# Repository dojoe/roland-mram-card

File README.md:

# Roland compatible multi-bank MRAM memory card

 (click to enlarge)

This is a replacement memory card for old Roland instruments of the late 80s and early 90s, such as the D-50 synthesizers, the JV-1080 and JV-2080 rack synths or the JD-880. It is meant to replace memory cards of the M-128, M-256 and M-512 lines (including M-256E, M-512G and all other suffixes). Some Akai devices from the same age actually use a compatible card format (BR-16 and BR-32) and this card will work in those too.

It doesn't need any kind of backup battery since it uses non-volatile MRAM for data storage, and thanks to the large memory chip used it emulates multiple virtual cards ("banks") which are selectable via slide switches - one of these memory cards will emulate 8x M-512 or 16x M-256 depending on the setting of a solder jumper.

The card has been developed with a lot of testing help from the community over at [the VintageSynth forums](https://forum.vintagesynth.com/viewtopic.php?f=24&t=76886) and over 900 units have been manufactured and sold since then - with near zero complaints :) Since the beginning of the project, we had plans to eventually publish the design data and source code for the card so it would stay available to everyone once we stopped making and selling them. So here it is!

## Compatibility

* **Tested and fully compatible:** Roland A-90, D-5, D-20, D-50, D-550, D-10, D-110, D-70, U-20, JD-800, JD-990, JV-880, JV-1000, JV-1080, JV-2080, R-880 (GC-8), R-8M, GR-1, GR-50, PM-16, TR-626, Akai MX-1000, VX600.
* **Mostly compatible:** Roland TD-10, TD-20. The card reportedly has errors when inserted all the way, but pulled back 1/8th of an inch it works fine.
* **Not compatible:** Roland VG-8, Peavey Tubefex.
* Some units like the Roland U-110 and U-220 only accept ROM cards, not RAM cards. Naturally, this RAM card replacement does not work in those, either.

## Differences to the cards we sell

Functionally, this design is 100% identical to the cards we sell online. I did make some changes to the appearance however to make homemade cards clearly distinguishable from ours.

Also, one part we use (a Bourns CAT25 SMD resistor network) is no longer being manufactured, so I updated the BOM with a Panasonic part as a drop-in replacement.

## Directories

* [mram-card](mram-card): The memory card hardware design files.
* [datasheets](datasheets): Data sheets for most of the parts used.
* [testbench](testbench): The testbench I'm using to test every card before they go out to customers.

## Making cards

Send the [KiCAD PCB file](mram-card/d50mram.kicad_pcb) or the [Gerbers](mram-card/gerbers.zip) to your favorite board house - or order directly from OSHPark:

<a href="https://oshpark.com/shared_projects/AyL7HCIK"></img></a>

As for parts, check out the [bill of materials](mram-card/d50mram.bom.csv).

Did you build one, or even more than one? We'd love to hear from you, feel free to leave a comment in the [card builder thread](https://github.com/dojoe/roland-mram-card/issues/2) :)

# Licenses

## Memory card

<br /><span xmlns:dct="http://purl.org/dc/terms/" property="dct:title">The hardware design of the <a href="https://github.com/dojoe/roland-mram-card">Roland compatible multi-bank MRAM memory card</a></span> by <a xmlns:cc="http://creativecommons.org/ns#" href="https://github.com/dojoe" property="cc:attributionName" rel="cc:attributionURL">Joachim "dojoe" Fenkes</a> is licensed under a <a rel="license" href="http://creativecommons.org/licenses/by-sa/4.0/">Creative Commons Attribution-ShareAlike 4.0 International License</a>.

## Testbench

Please see the [testbench README](testbench/README.md) for testbench license information.

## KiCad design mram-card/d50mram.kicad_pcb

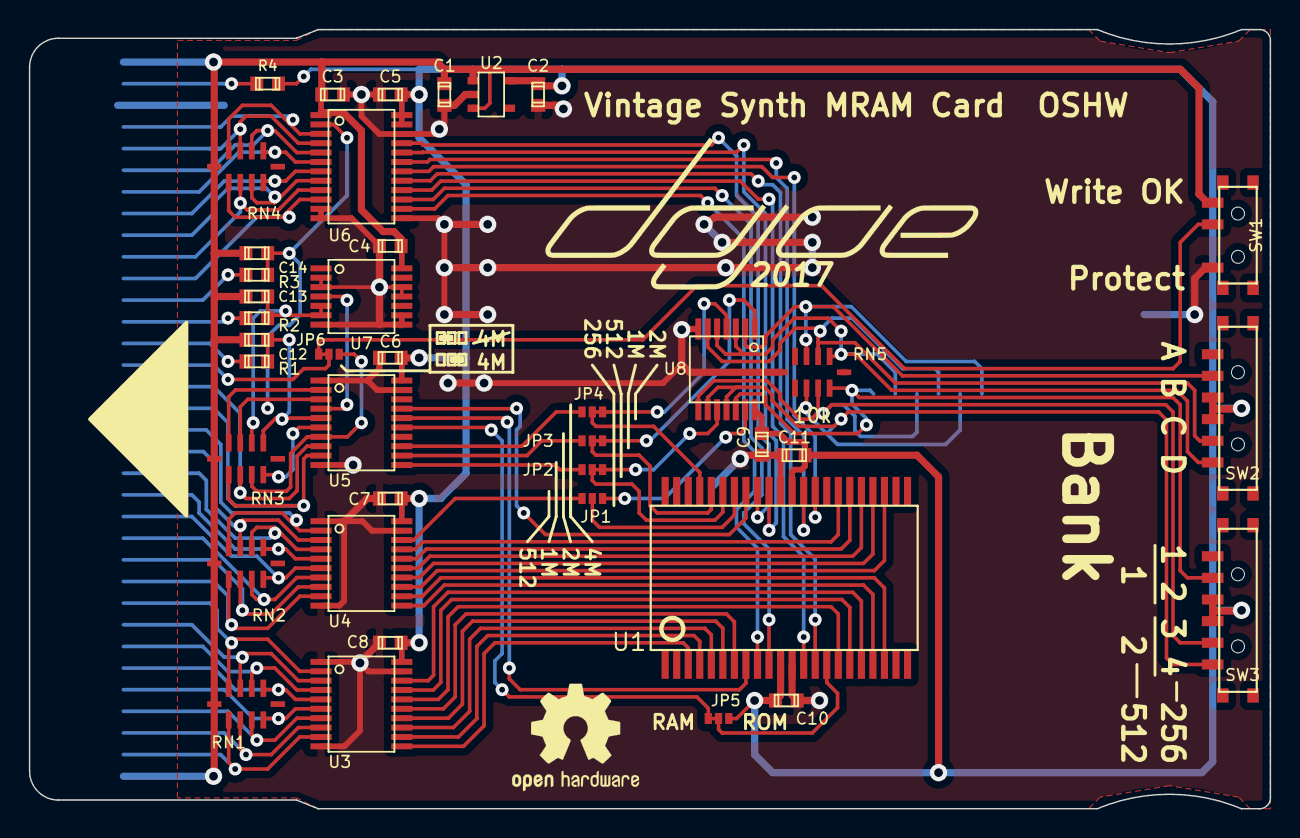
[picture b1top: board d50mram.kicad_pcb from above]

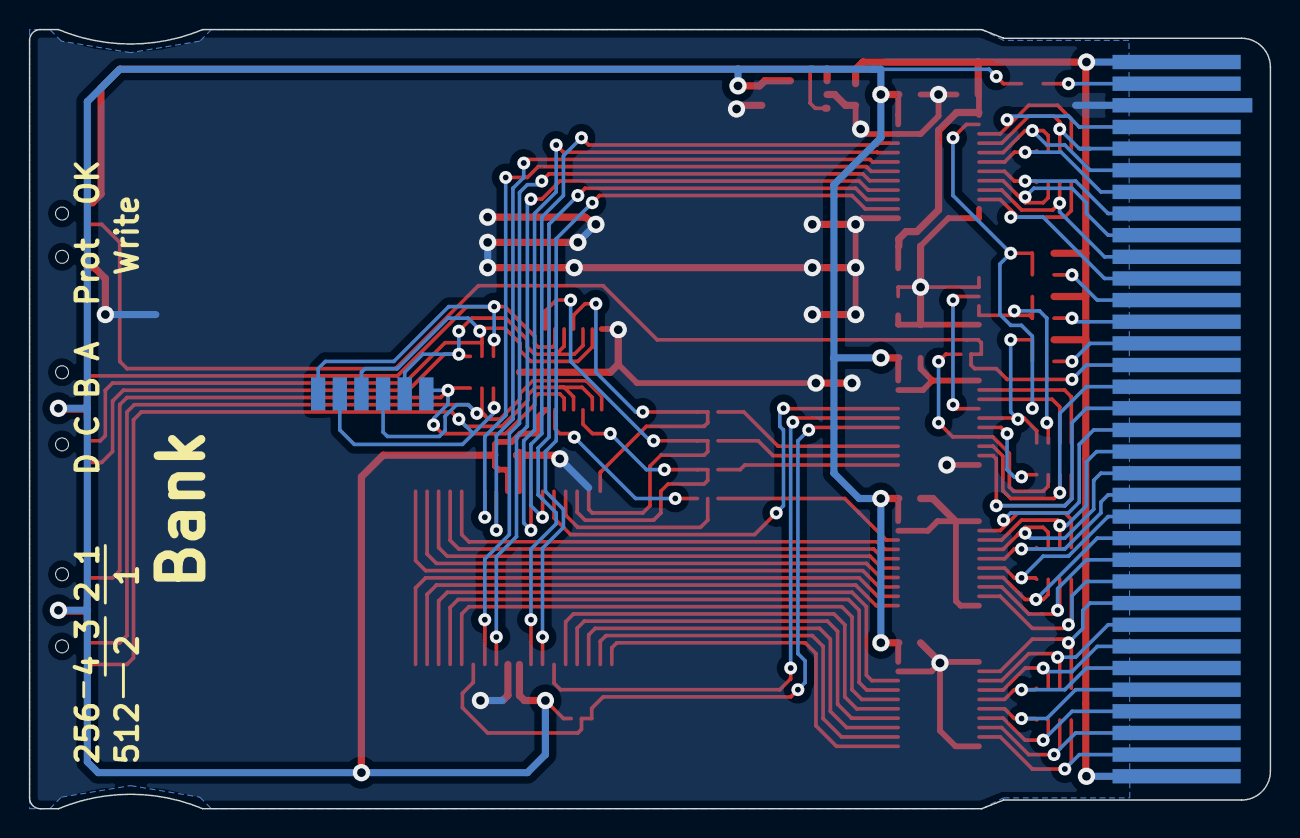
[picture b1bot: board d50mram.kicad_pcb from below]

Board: 2 copper layers, 86.0 x 54.0 mm, 43 parts (2 on the bottom side), 82 nets.

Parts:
C1, C2: 1uF X7R; c_0603
C3, C4, C5, C6, C7, C8, C9, C10, C11: 100n; c_0603
C12, C13, C14: 100p; c_0603
J1: D50-EDGECONN; EDGE1S34
JP1, JP2, JP3, JP4, JP5, JP6: JUMPER3; S_JUMPER_3
R1, R2, R3, R4: 100R; c_0603
RN1, RN2, RN3, RN4, RN5: 10k; CAT25
SW1: SPDT; CUS-12B
SW2, SW3: SP4T; CUS-14B
TP1: CONN_6; 6P_TESTPT
U1: EST-MR2A08A; TSOP2-44
U2: MIC5265-3.3YD5; SOT23-5
U3, U4, U5: 74LVX541; tssop-20
U6: 74LVX4245; tssop-24
U7, U8: 74HC02; tssop-14
VAL: REF; dojoe

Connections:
+3.3V: C2.1, C5.1, C6.1, C7.1, C8.1, C9.1, C10.1, C11.1, JP5.1, R4.2, SW2.1, SW3.1, U1.11, U1.33, U2.5, U3.20, U4.20, U5.20, U6.23, U6.24, U8.14
+5V: C1.1, C3.1, C4.1, C12.2, C13.2, C14.2, J1.1, J1.34, RN1.1, RN2.1, RN3.1, RN4.1, SW1.2, U2.1, U2.3, U6.1, U7.14
/A0C: J1.2, RN1.7, U3.9
/A0M: U1.3, U3.11
/A1C: J1.3, RN1.8, U3.8
/A1M: U1.4, U3.12
/A2C: J1.4, RN1.9, U3.7
/A2M: U1.5, U3.13
/A3C: J1.5, RN1.10, U3.6
/A3M: U1.6, U3.14
/A4C: J1.6, RN1.2, U3.5
/A4M: U1.7, U3.15
/A5C: J1.7, RN1.3, U3.4
/A5M: U1.16, U3.16
/A6C: J1.8, RN1.4, U3.3
/A6M: U1.17, U3.17
/A7C: J1.9, RN1.5, U3.2
/A7M: U1.18, U3.18
/A8C: J1.10, RN2.7, U4.9
/A8M: U1.19, U4.11
/A9C: J1.11, RN2.8, U4.8
/A9M: U1.20, U4.12
/A10C: J1.12, RN2.9, U4.7
/A10M: U1.25, U4.13
/A11C: J1.13, RN2.10, U4.6
/A11M: U1.26, U4.14
/A12C: J1.14, RN2.2, U4.5
/A12M: U1.27, U4.15
/A13C: J1.15, RN2.3, U4.4
/A13M: U1.28, U4.16
/A14C: J1.16, RN2.4, U4.3
/A14M: U1.29, U4.17
/A15C: J1.17, RN2.5, U4.2
/A15M: JP1.2, U1.38
/A15M_C: JP1.1, U4.18
/A15M_SW: JP1.3, U8.13
/A16C: J1.18, RN3.7, U5.9
/A16M: JP2.2, JP2.3, U1.39, U8.10
/A16M_C: JP2.1, U5.11
/A17C: J1.19, RN3.8, U5.8
/A17M: JP3.2, JP3.3, U1.40, U8.1
/A17M_C: JP3.1, U5.12
/A18C: JP6.3, RN3.9, U5.7
/A18M: JP4.2, JP4.3, U1.41, U8.4
/A18M_C: JP4.1, U5.13
/BANK2: RN5.5, SW3.3, TP1.1, U8.12
/BANK3: RN5.4, SW3.4, TP1.3, U8.8
/BANK4: RN5.3, SW3.5, TP1.5, U8.9, U8.11
/BANKB: RN5.9, SW2.3, TP1.6, U8.2
/BANKC: RN5.8, SW2.4, TP1.4, U8.6
/BANKD: RN5.7, SW2.5, TP1.2, U8.3, U8.5
/CEC: J1.22, R2.1
/D0C: J1.24, RN4.7, U6.10
/D0M: U1.9, U6.14
/D1C: J1.25, RN4.8, U6.9
/D1M: U1.10, U6.15
/D2C: J1.26, RN4.9, U6.8
/D2M: U1.13, U6.16
/D3C: J1.27, RN4.10, U6.7
/D3M: U1.14, U6.17
/D4C: J1.28, RN4.2, U6.6
/D4M: U1.31, U6.18
/D5C: J1.29, RN4.3, U6.5
/D5M: U1.32, U6.19
/D6C: J1.30, RN4.4, U6.4
/D6M: U1.35, U6.20
/D7C: J1.31, RN4.5, U6.3
/D7M: U1.36, U6.21
/WR_EN: J1.20, JP6.1, JP6.2, SW1.1
/~CEC: U5.4, U7.4
/~CEM: U1.8, U5.16
/~OEC: J1.23, R3.1
/~OEM: U1.37, U5.17
/~WEC: J1.21, R1.1
/~WEM: JP5.2, JP5.3, U1.15, U5.15
GND: C1.2, C2.2, C3.2, C4.2, C5.2, C6.2, C7.2, C8.2, C9.2, C10.2, C11.2, J1.32, RN5.1, SW1.3, U1.12, U1.34, U2.2, U3.1, U3.10, U3.19, U4.1, U4.10, U4.19, U5.1, U5.10, U5.19, U6.11, U6.12, U6.13, U6.22, U7.2, U7.3, U7.7, U7.8, U7.9, U7.11, U7.12, U8.7
unnamed: C12.1, R1.2, RN3.2, U5.5
unnamed: C13.1, R2.2, RN3.3, U7.5, U7.6
unnamed: C14.1, R3.2, RN3.4, U5.3, U6.2
unnamed: J1.33, R4.1
unnamed: RN3.5, U5.2
unnamed: RN3.10, U5.6

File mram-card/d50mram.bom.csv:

"Source:","D:\Projects\d50_mram_card\opensource\mram-card\d50mram.kicad_sch"
"Date:","2023-01-02 14:01:17"
"Tool:","Eeschema (6.0.7)"
"Generator:","C:\Program Files\KiCad\6.0\bin\scripting\plugins/bom_csv_grouped_by_value.py"
"Component Count:","42"

"Individual Components:"

"Item","Qty","Reference(s)","Value","LibPart","Footprint","Datasheet","Digikey","Mouser"
"","","C1","1uF X7R","d50mram:C","","","",""
"","","C2","1uF X7R","d50mram:C","","","",""
"","","C3","100n","d50mram:C","","","",""
"","","C4","100n","d50mram:C","","","",""
"","","C5","100n","d50mram:C","","","",""
"","","C6","100n","d50mram:C","","","",""
"","","C7","100n","d50mram:C","","","",""
"","","C8","100n","d50mram:C","","","",""
"","","C9","100n","d50mram:C","","","",""
"","","C10","100n","d50mram:C","","","",""
"","","C11","100n","d50mram:C","","","",""
"","","C12","100p","d50mram:C","","","",""
"","","C13","100p","d50mram:C","","","",""
"","","C14","100p","d50mram:C","","","",""
"","","J1","D50-EDGECONN","d50mram:D50-EDGECONN","","","",""
"","","JP1","JUMPER3","d50mram:JUMPER3","","","",""
"","","JP2","JUMPER3","d50mram:JUMPER3","","","",""
"","","JP3","JUMPER3","d50mram:JUMPER3","","","",""
"","","JP4","JUMPER3","d50mram:JUMPER3","","","",""
"","","JP5","JUMPER3","d50mram:JUMPER3","","","",""
"","","JP6","JUMPER3","d50mram:JUMPER3","","","",""
"","","R1","100R","d50mram:R","","","",""
"","","R2","100R","d50mram:R","","","",""
"","","R3","100R","d50mram:R","","","",""
"","","R4","100R","d50mram:R","","","",""
"","","RN1","10k","d50mram:CAT25","","","U8103CT-ND","667-EXB-E10C103J"
"","","RN2","10k","d50mram:CAT25","","","U8103CT-ND","667-EXB-E10C103J"
"","","RN3","10k","d50mram:CAT25","","","U8103CT-ND","667-EXB-E10C103J"
"","","RN4","10k","d50mram:CAT25","","","U8103CT-ND","667-EXB-E10C103J"
"","","RN5","10k","d50mram:CAT25","","","U8103CT-ND","667-EXB-E10C103J"
"","","SW1","SPDT","d50mram:SPDT","","","563-1102-1-ND","229-CUS-12TB"
"","","SW2","SP4T","d50mram:SP4T","","","563-1104-1-ND","229-CUS-14TB"
"","","SW3","SP4T","d50mram:SP4T","","","563-1104-1-ND","229-CUS-14TB"
"","","TP1","CONN_6","d50mram:CONN_6","","","",""
"","","U1","EST-MR2A08A","d50mram:EST-MR2A08A","","","819-1004-ND","936-MR2A08AYS35"
"","","U2","MIC5265-3.3YD5","d50mram:TC1054","","","576-2835-1-ND","998-MIC5265-3.3YD5TR"
"","","U3","74LVX541","d50mram:74LS541","","","74LVX541MTCXCT-ND","512-74LVX541MTCX"
"","","U4","74LVX541","d50mram:74LS541","","","74LVX541MTCXCT-ND","512-74LVX541MTCX"
"","","U5","74LVX541","d50mram:74LS541","","","74LVX541MTCXCT-ND","512-74LVX541MTCX"
"","","U6","74LVX4245","d50mram:74x4245","","","74LVX4245MTCXCT-ND","512-74LVX4245MTCX"
"","","U7","74HC02","d50mram:74LS02P","","","MM74HC02MTCXCT-ND","512-MM74HC02MTCX"
"","","U8","74HC02","d50mram:74LS02P","","","MM74HC02MTCXCT-ND","512-MM74HC02MTCX"



"Collated Components:"

"Item","Qty","Reference(s)","Value","LibPart","Footprint","Datasheet","Digikey","Mouser"
"1","2","C1, C2","1uF X7R","d50mram:C","","","",""
"2","9","C3, C4, C5, C6, C7, C8, C9, C10, C11","100n","d50mram:C","","","",""
"3","3","C12, C13, C14","100p","d50mram:C","","","",""
"4","1","J1","D50-EDGECONN","d50mram:D50-EDGECONN","","","",""
"5","6","JP1, JP2, JP3, JP4, JP5, JP6","JUMPER3","d50mram:JUMPER3","","","",""
"6","4","R1, R2, R3, R4","100R","d50mram:R","","","",""
"7","5","RN1, RN2, RN3, RN4, RN5","10k","d50mram:CAT25","","","U8103CT-ND","667-EXB-E10C103J"
"8","1","SW1","SPDT","d50mram:SPDT","","","563-1102-1-ND","229-CUS-12TB"
"9","2","SW2, SW3","SP4T","d50mram:SP4T","","","563-1104-1-ND","229-CUS-14TB"
"10","1","TP1","CONN_6","d50mram:CONN_6","","","",""
"11","1","U1","EST-MR2A08A","d50mram:EST-MR2A08A","","","819-1004-ND","936-MR2A08AYS35"
"12","1","U2","MIC5265-3.3YD5","d50mram:TC1054","","","576-2835-1-ND","998-MIC5265-3.3YD5TR"
"13","3","U3, U4, U5","74LVX541","d50mram:74LS541","","","74LVX541MTCXCT-ND","512-74LVX541MTCX"
"14","1","U6","74LVX4245","d50mram:74x4245","","","74LVX4245MTCXCT-ND","512-74LVX4245MTCX"
"15","2","U7, U8","74HC02","d50mram:74LS02P","","","MM74HC02MTCXCT-ND","512-MM74HC02MTCX"

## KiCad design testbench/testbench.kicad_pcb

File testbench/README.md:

# Roland Memory Card Testbench

 (click to enlarge)

This is a quick and dirty test jig I built to test the memory card. It performs these tests, in order:

1. Check voltage rails (5V provided from outside, 3.3V generated on the card).
2. Single bank full read/write with data checking to test address and data lines.
3. Test write protect and bank switches - the user is prompted to operate the switches while the test program monitors the switch positions.
4. Verify bank switching logic - while the bank switches are tested, the test program writes a byte value identifying the bank to each and checks in a second pass that all values are read back correctly.

In addition to that it also has a couple debugging features: It can write and read memory cards (one bank at a time) and dump the current value of all microcontroller IO ports to the serial console (to test the test jig itself).

# Hardware

The test jig is built around my ATMega32U4 mini breakout board, the TinyMega - any 32U4 based Arduino board should do the trick though. I updated the schematics to reflect a more generic ATMega32U4 and added the user LED and user button that are connected to pins E6 and E2 on my board respectively.

**The PCB layout is only for illustrative purposes and not recommended for use!** It no longer matches the schematics, does not reflect some board modifications I have made in the meantime, and generally is a quick single-sided abomination I whacked together to get a test jig made over the weekend :) You can copy the arrangement of the spring contacts but should really redesign the rest from scratch.

Speaking of which, the spring contacts I've used are ["Micro Universal Contact Z 2.5mm"](../datasheets/springcontact.pdf) by ITT Cannon, Digikey P/N 120220-0312.

As you can see when looking at the schematics, the test jig uses every single I/O pin of the microcontroller. Address bits A0..A15 are generated via a chain of 74HC595 shift registers, all other signals are operated and monitored directly. Pin E6 ends up doing double duty - usually it just drives the LED to indicate test progress but a special 1Mbit write/dump mode was added later on that uses this pin for an additional address line.

A P-MOSFET is used to turn power to the card under test on and off; the small series resistor R2 limits the current in case of a short or near-short on the card. It will also cause a significant voltage drop in case the card isn't shorted but draws more current than expected - this will be detected in step 1 above and will fail the test.

The memory card has six test points that are used to read back the position of the four-way slide switches. The test program will poll these (with some debouncing logic) to pace the progress of steps 3+4 above in lockstep with the user moving the switches.

# Software

The test program is as quick and dirty a hack as is the hardware - it is based on the VirtualSerial demo program from the LUFA USB library, with almost no modifications to the USB serial code. All the test code is contained within [test.c](firmware/test.c), which is the only file _not_ shamelessly yoinked from LUFA.

The test program has four modes:

* Test mode, which will execute the test sequence.
* Dump mode, which will dump the entire card content to the serial console as a binary stream.
* Program mode, which will write binary data coming in via the serial console to the card.
* DIO monitor mode, which will keep printing the state of the I/O ports to the serial console.

For Test, Dump and Program mode, you can additionally select a card size; Test mode supports 256 and 512 kbit, Dump and Program modes additionally support 128 and 1024 kbit cards. The default upon startup is Test mode for 256 kbit cards.

You can switch modes by sending characters over the serial link: t, p, d, m select Test, Program, Dump and Monitor mode respectively, and 1..4 select 128, 256, 512 and 1024 kbit sizes.

To connect to the test jig, use a simple terminal program like [RealTerm](https://realterm.sourceforge.io/).

Regardless of mode, pushing the user button starts an operation.

## Test mode

Once you push the button, the test program will run through the tests in this order:

1. Turn off the user LED (in case it was turned on)
2. Test voltage rails
3. Check that all slide switches are in the right position (write protect off, bank A1 selected)
4. Read/write test of bank A1
5. Detect card size, fail if detected size doesn't match what's configured via serial
6. Turn on the user LED to indicate progress to the user
7. Test write protect switch: User must turn write protect on, then off again
8. Turn the user LED back off
9. Test ABCD bank switch: User must move switch through all positions from A thru D and then back again
10. Test 1234 bank switch in the same way
11. If we get here without error, the test passes - turn on the user LED to indicate success

If any of these steps fails, the test will abort and the user LED will blink. Also, whenever the program is waiting for user action, the user can instead push the button to abort the test.

## Dump mode

Once you push the button, the test program will read the entire card and output the contents to the serial link as a stream of bytes. The idea is that you configure dump mode and the correct size via your terminal program, then start a capture to file in the terminal program and push the button.

## Program mode

This is similar to Dump mode, except that your terminal program will be the one sending bytes to the test jig. As you push the button, the test program will print a message prompting you to send data, then you can have your terminal program send a binary file directly to the serial line. The test program will expect exactly as many bytes as you set up earlier.

# Licenses

 <p xmlns:cc="http://creativecommons.org/ns#" xmlns:dct="http://purl.org/dc/terms/">The hardware (schematics, example layout) of <a property="dct:title" rel="cc:attributionURL" href="https://github.com/dojoe/roland-mram-card/tree/master/testbench">Roland Memory Card Testbench</a> by <a rel="cc:attributionURL dct:creator" property="cc:attributionName" href="https://github.com/dojoe">Joachim "dojoe" Fenkes</a> is marked with <a href="http://creativecommons.org/publicdomain/zero/1.0?ref=chooser-v1" target="_blank" rel="license noopener noreferrer" style="display:inline-block;">CC0 1.0</a></p>

The actual test code, [test.c](firmware/test.c), is licensed under [the Unlicense](https://unlicense.org).

All other code in the firmware directory is copied or adapted from [LUFA](http://www.fourwalledcubicle.com/LUFA.php) and covered by [LUFA's license](firmware/LUFA/License.txt).

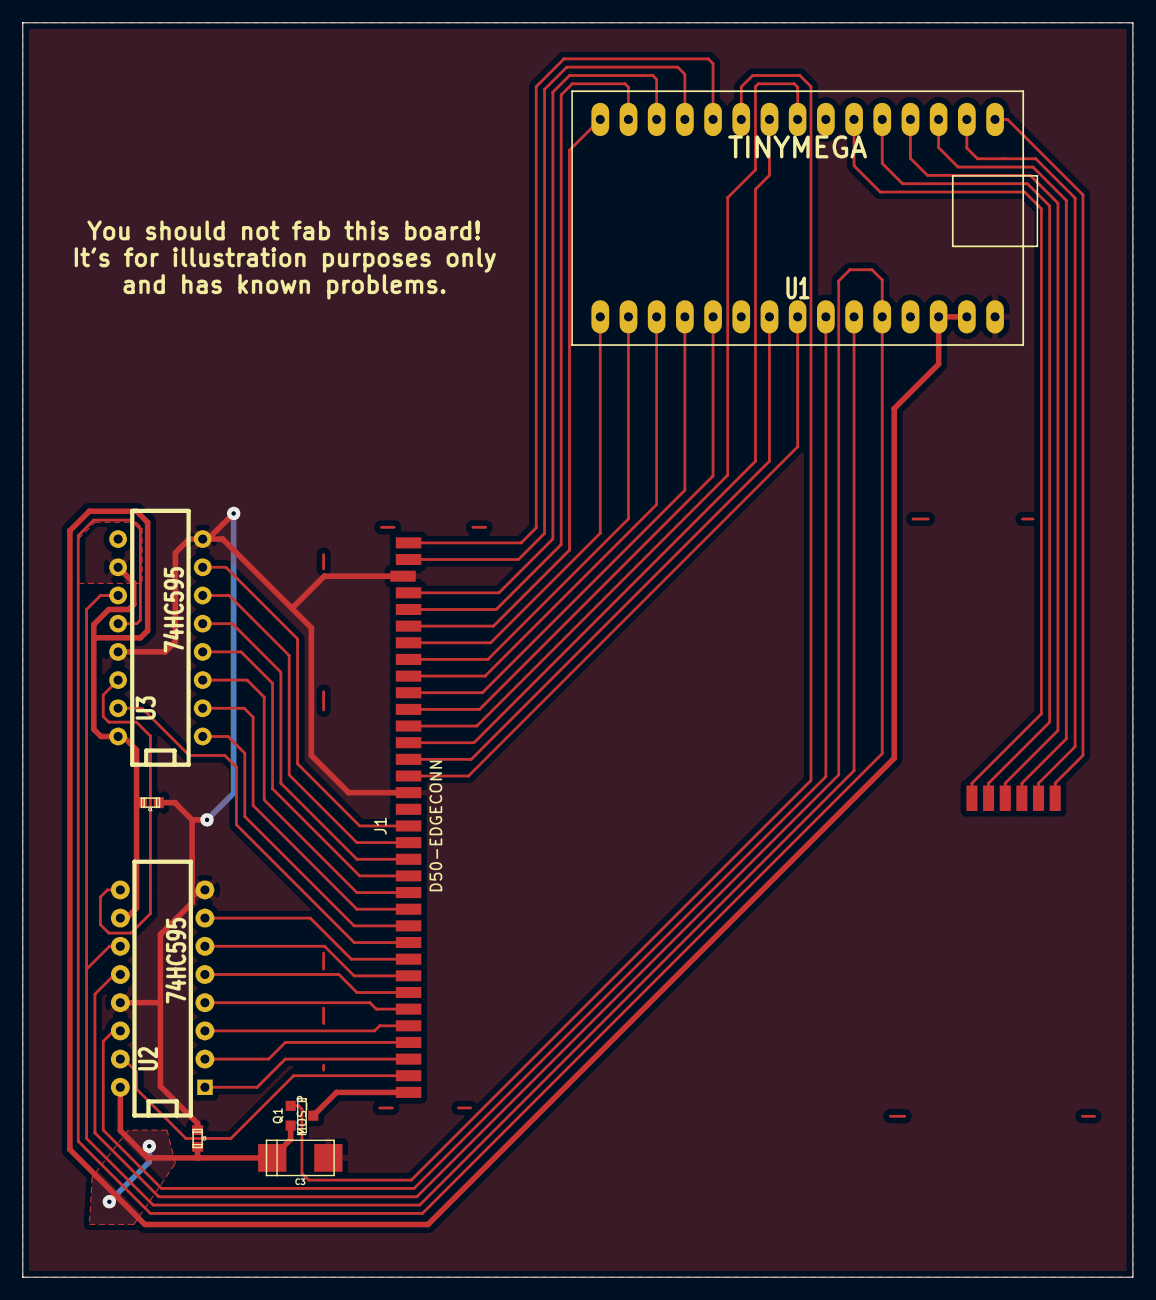
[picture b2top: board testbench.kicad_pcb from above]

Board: 2 copper layers, 100.0 x 113.0 mm, 9 parts (0 on the bottom side), 45 nets.

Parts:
C1, C2: 100n; c_0603
C3: 4u7; c_tant_C
J1: D50-EDGECONN; d50conn_test
J2: CONN_6; 6P_TESTPT
Q1: MOS_P; SOT23GDS
U1: TINYMEGA; TinyMega
U2, U3: 74HC595; DIP-16__300

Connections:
+5V: C1.1, C2.1, C3.1, Q1.S, U1.2, U1.3, U2.10, U2.16, U3.10, U3.16
/A16: J1.18, U1.4
GND: C1.2, C2.2, C3.2, J1.19, J1.32, U1.1, U2.8, U2.13, U3.8, U3.13
unnamed: J1.1, Q1.D
unnamed: J1.2, U2.15
unnamed: J1.3, U2.1
unnamed: J1.4, U2.2
unnamed: J1.5, U2.3
unnamed: J1.6, U2.4
unnamed: J1.7, U2.5
unnamed: J1.8, U2.6
unnamed: J1.9, U2.7
unnamed: J1.10, U3.15
unnamed: J1.11, U3.1
unnamed: J1.12, U3.2
unnamed: J1.13, U3.3
unnamed: J1.14, U3.4
unnamed: J1.15, U3.5
unnamed: J1.16, U3.6
unnamed: J1.17, U3.7
unnamed: J1.20, U1.8
unnamed: J1.21, U1.9
unnamed: J1.22, U1.22
unnamed: J1.23, U1.23
unnamed: J1.24, U1.11
unnamed: J1.25, U1.12
unnamed: J1.26, U1.13
unnamed: J1.27, U1.14
unnamed: J1.28, U1.15
unnamed: J1.29, U1.16
unnamed: J1.30, U1.17
unnamed: J1.31, U1.18
unnamed: J1.33, U1.19
unnamed: J1.34, U1.20
unnamed: J2.1, U1.25
unnamed: J2.2, U1.26
unnamed: J2.3, U1.27
unnamed: J2.4, U1.28
unnamed: J2.5, U1.29
unnamed: J2.6, U1.30
unnamed: Q1.G, U1.21
unnamed: U1.5, U2.12, U3.12
unnamed: U1.6, U2.11, U3.11
unnamed: U1.7, U2.14
unnamed: U2.9, U3.14

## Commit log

2021-12-24 Initial open-source release
2022-02-11 Update README with confirmed D-20 support
2022-02-23 Replacement resistor networks work fine!
    Thanks a lot to @MrMojoRisinGottaKeepOnRisin for reporting back!
2022-02-23 Add a guestbook :)
2022-07-07 Added Mouser part numbers to BOM
2022-07-07 Fixed delimiter
2023-01-02 Update to KiCad 6, add Mouser part numbers
    Also add a note stating that MIC5245 is a valid replacement
    for the MIC5265.
    Thanks to @HSBallina for all the parts sleuthing!
    Closes #4.
